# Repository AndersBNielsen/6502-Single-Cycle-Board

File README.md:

# 6502 Single Cycle Board
 Easy 6502 Single Stepping based on Steve Wozniak's circuit in the Apple-1 Manual

Hook up 5V+GND and the three signals to your 6502 CPU and watch it halt after each instruction - even running at several MHz. No matter if it's an NMOS 6502 from 1975 or a CMOS from 2024. 

You can either order the PCB from JLCPCB (shipping world wide, see below) who kindly sponsored this project or order a ready made board direct from the creator here(shipping to 51 countries): https://www.imania.dk/index.php?cPath=204&sort=5a&language=en

## Ordering a PCB worldwide
This project is kindly sponsored by JLCPCB. They offer cheap, professional looking PCBs and super fast delivery.

Step 1: Get the gerber file zip package from this repo
https://github.com/AndersBNielsen/6502-Single-Cycle-Board/blob/main/6502SCB.zip

Step 2: Upload to JLCPCB [https://jlcpcb.com/?from=Anders_N](https://jlcpcb.com/?from=Anders_N)

Step 3: Pick your color, surface finish and order.

You can use these affiliate links to get a board for $2 and also get $54 worth of New User Coupons at: https://jlcpcb.com/?from=Anders_N

And in case you also want to order a 3D-printed case you can use this link. 
How to Get a $7 3D Printing Coupon: [https://jlc3dp.com/?from=Anders_N](https://jlc3dp.com/?from=Anders_N)

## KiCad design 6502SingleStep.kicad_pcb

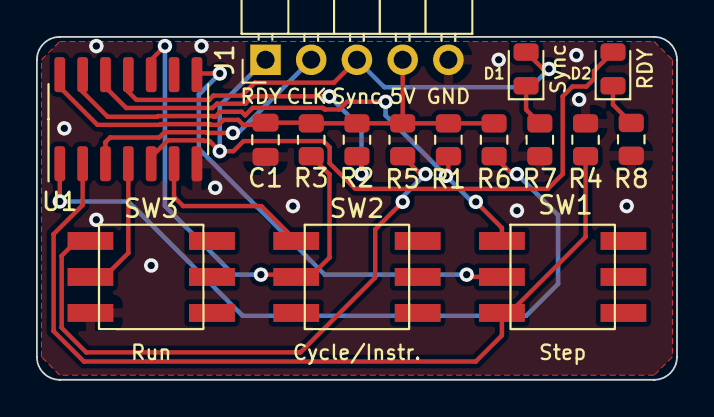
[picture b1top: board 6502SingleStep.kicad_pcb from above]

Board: 2 copper layers, 35.6 x 19.0 mm, 16 parts (0 on the bottom side), 16 nets.

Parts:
C1: C_Small; C_0805_2012Metric
D1, D2: LED; LED_0805_2012Metric
J1: Conn_01x05_Male; PinHeader_1x05_P2.54mm_Horizontal
R1, R2, R3, R5, R6, R7, R8: 4k7; R_0805_2012Metric
R4: 300; R_0805_2012Metric
SW1: Step; XKB5858
SW2: Single Instruction; XKB5858
SW3: RUN; XKB5858
U1: 74HC74; SO-14_3.9x8.65mm_P1.27mm

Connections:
+5V: C1.1, J1.4, R1.1, R2.1, R3.1, R5.1, R6.1, U1.14 (VCC)
CLK: J1.2, U1.3 (C)
GND: C1.2, J1.5, R4.2, R7.2, R8.2, SW3.3 (C), U1.7 (GND)
unnamed: D1.1 (K), R7.1
unnamed: D2.1 (K), R8.1
unnamed: R1.2, SW1.1 (A), U1.13 (~R)
unnamed: R2.2, U1.12 (D)
unnamed: R3.2, SW2.2 (B), U1.10 (~S)
unnamed: R4.1, SW1.3 (C), U1.2 (D)
unnamed: R5.2, SW3.1 (A)
unnamed: R6.2, U1.1 (~R)
unnamed: SW1.2 (B), U1.8 (~Q)
unnamed: SW2.1 (A), U1.6 (~Q)
unnamed: SW3.2 (B), U1.4 (~S)
RDY: D2.2 (A), J1.1, U1.5 (Q)
SYNC: D1.2 (A), J1.3, U1.11 (C)

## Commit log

2024-07-16 KiCAD Source
2024-07-16 Update README.md
    Ordering information
